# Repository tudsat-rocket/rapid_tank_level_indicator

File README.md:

# rapid_tank_level_indicator
Flex PCB to be mounted to the outside of the rocket's propellant tank to measure it's fillig level.

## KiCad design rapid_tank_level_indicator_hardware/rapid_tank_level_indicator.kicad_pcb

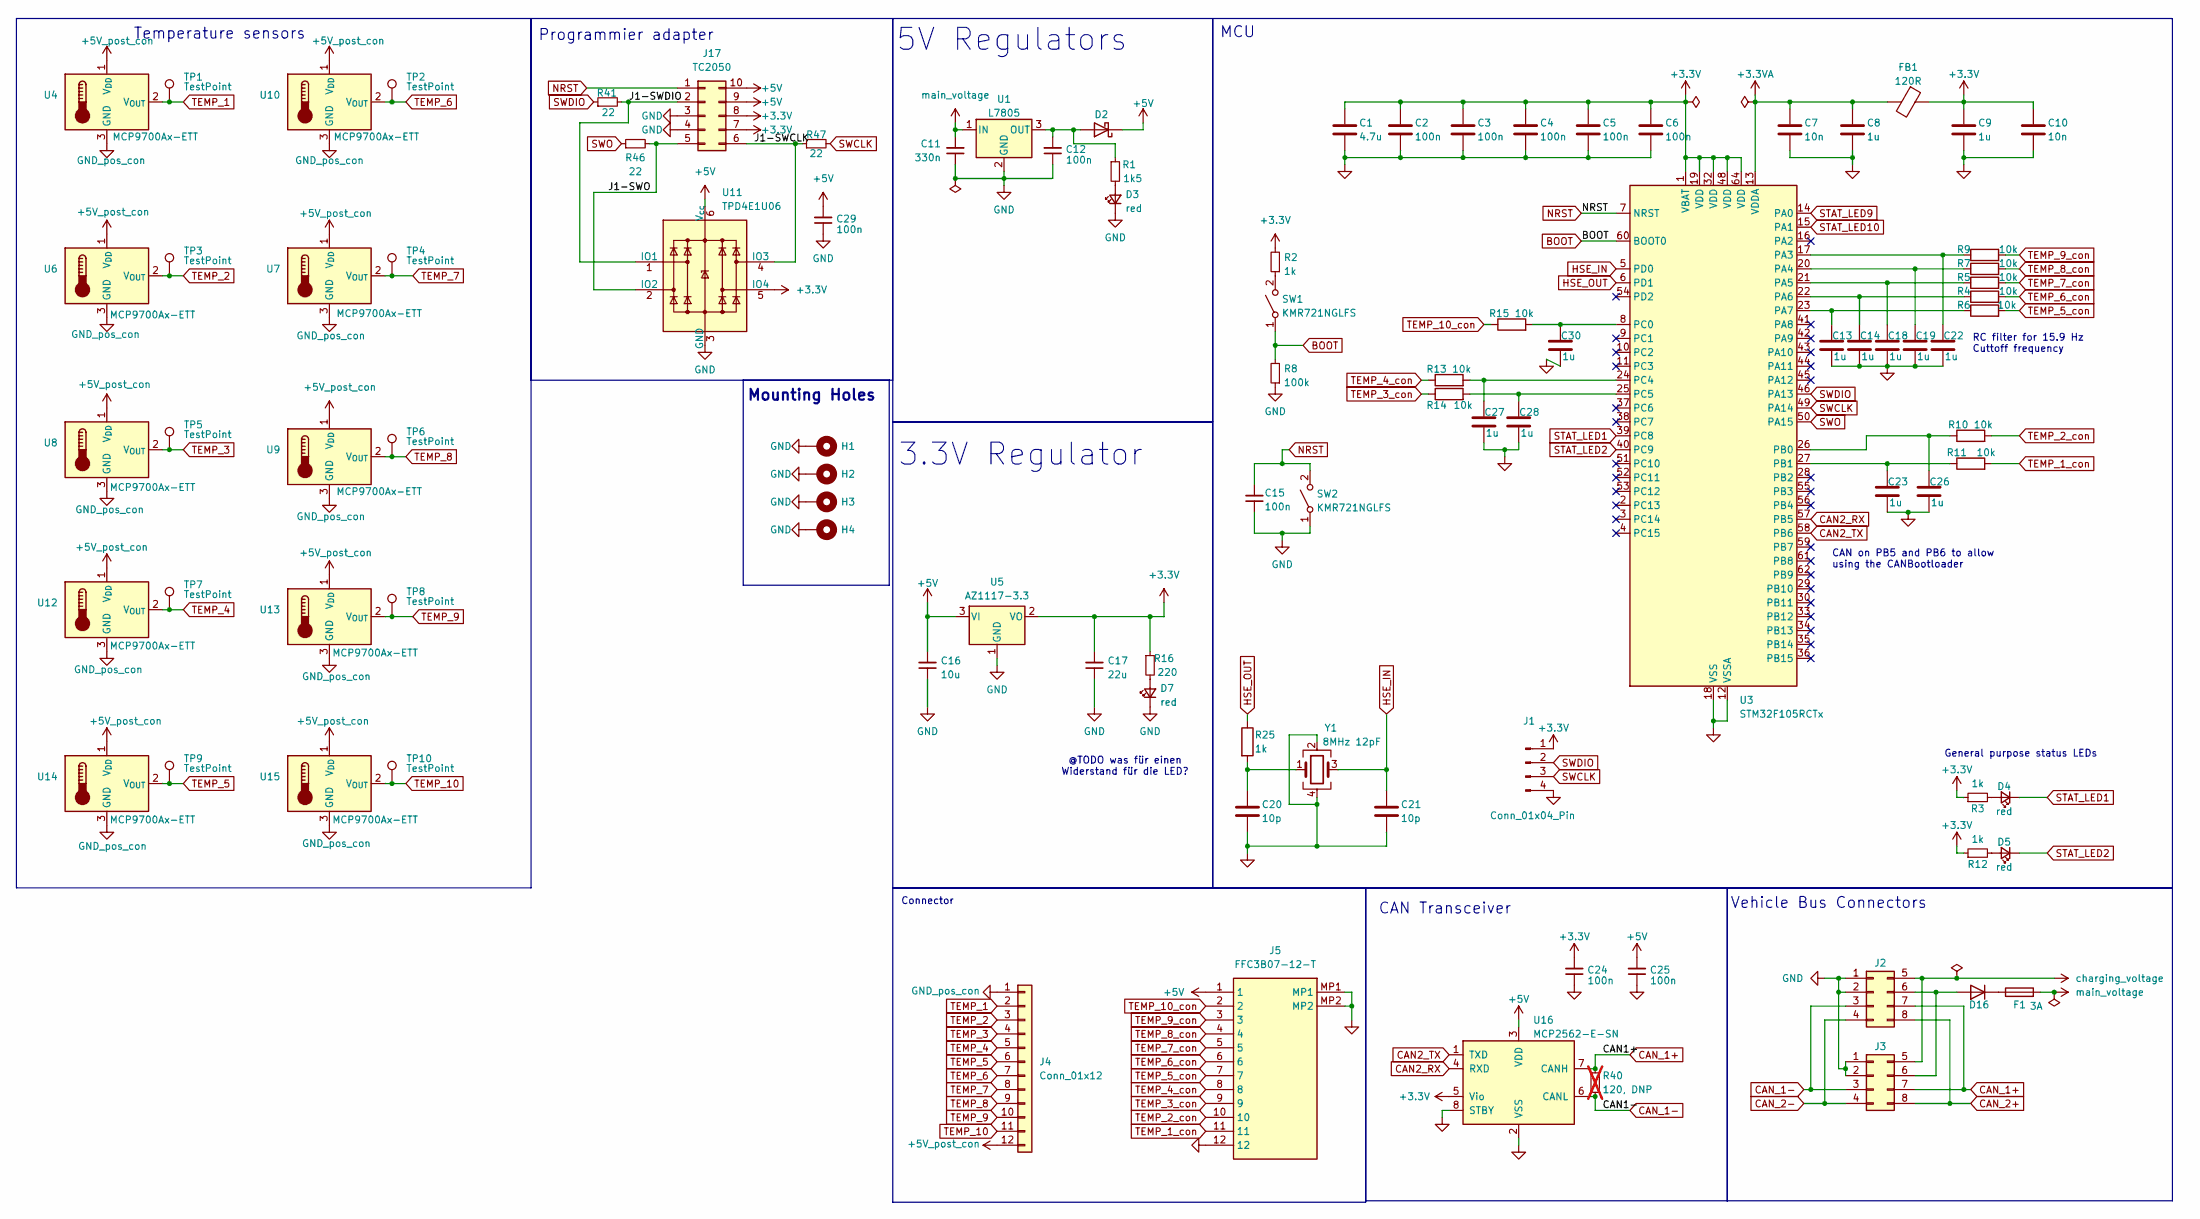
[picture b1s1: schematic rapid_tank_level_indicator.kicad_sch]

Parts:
C1: 4.7u; C_0402_1005Metric; LCSC# C368809
C2, C3, C4, C5, C6, C12, C24, C25, C29: 100n; C_0402_1005Metric; LCSC# C77020
C7, C10: 10n; C_0402_1005Metric; LCSC# C60133
C8, C9: 1u; C_0402_1005Metric; LCSC# C52923
C11: 330n; C_0603_1608Metric; Part# CL10B334KO8NNNC; LCSC# C159798
C13, C14, C18, C19, C22, C23, C26, C27, C28, C30: 1u; C_0402_1005Metric
C15: 100n; C_0402_1005Metric; Part# CL10B104KB8NNNC; LCSC C1525
C16: 10u; C_0402_1005Metric; Part# CL31B106KAHNNNE; LCSC C76991
C17: 22u; C_0402_1005Metric; Part# GRM155R60J226ME11D; LCSC C415703
C20, C21: 10p; C_0402_1005Metric; LCSC# C76946
D2: RB070MM-30TR; D_SOD-123F; LCSC # C162059
D3: red; LED_0603_1608Metric; LCSC# C2286
D4, D5: red; LED_0603_1608Metric; LCSC C2286
D7: red; LED_0603_1608Metric; Part# 19-213/RSC-BS2T2B/3T; LCSC# C474026
D16: D; D_SMA; LCSC# C5140034
F1: 3A; Fuse_0603_1608Metric_Pad1.05x0.95mm_HandSolder; LCSC# C311062
FB1: 120R; L_0603_1608Metric; Part# BLM18PG121SN1D; LCSC# C14709
H1, H2, H3, H4: MountingHole_Pad; MountingHole_3.2mm_M3_Pad_Via; Part# N/A; DigiKey# N/A
J1: Conn_01x04_Pin; PinHeader_1x04_P1.27mm_Vertical_SMD_Pin1Left
J2, J3: Conn_02x04_Top_Bottom; Molex_Micro-Fit_3.0_43045-0800_2x04_P3.00mm_Horizontal; LCSC# x
J4: Conn_01x12; FFC3B07_pad
J5: FFC3B07-12-T; FFC3B0712T; Mouser Part Number 640-FFC3B07-12-T
J17: TC2050; Tag-Connect_TC2050-IDC-FP_2x05_P1.27mm_Vertical; LCSC# x
R1: 1k5; R_0402_1005Metric; Part# ESR03EZPJ221; LCSC# C112291
R2: 1k; R_0402_1005Metric; Part# RC0603FR-0710KL; LCSC C11702
R3, R12: 1k; R_0402_1005Metric; LCSC C11702
R4, R5, R6, R7, R9, R10, R11, R13, R14, R15: 10k; R_0402_1005Metric
R8: 100k; R_0402_1005Metric; Part# RC0603FR-0710KL; LCSC C25741
R16: 220; R_0402_1005Metric; Part# ESR03EZPJ221; LCSC# C112291
R25: 1k; R_0402_1005Metric; LCSC# C21190
R40: 120, DNP; R_0603_1608Metric_Pad0.98x0.95mm_HandSolder; LCSC# x; not fitted
R41, R46, R47: 22; R_0402_1005Metric; Part# RC0603FR-0710KL; LCSC C25092
SW1, SW2: KMR721NGLFS; SW_Push_1P1T_NO_CK_KMR2; Part# KMR721NGLFS; LCSC C2911418
TP1, TP2, TP3, TP4, TP5, TP6, TP7, TP8, TP9, TP10: TestPoint; TestPoint_Pad_D1.0mm
U1: L7805; TO-252-2; Part# L7805CDT-TR; LCSC# C310413
U3: STM32F105RCTx; LQFP-64_10x10mm_P0.5mm; LCSC# C8345
U4, U6, U7, U8, U9, U10, U12, U13, U14, U15: MCP9700Ax-ETT; SOT-23; LCSC C127949
U5: AZ1117-3.3; SOT-223-3_TabPin2; LCSC C92102
U11: TPD4E1U06; SOT-563; LCSC C527516
U16: MCP2562-E-SN; SOIC-8_3.9x4.9mm_P1.27mm; Part# MCP2562T-E/SN; LCSC# C191417
Y1: 8MHz 12pF; Crystal_SMD_5032-4Pin_5.0x3.2mm; Part# 5TJ480000NYLBC; LCSC# C2149245

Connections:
+3.3V: C1.1, C2.1, C3.1, C4.1, C5.1, C6.1, C9.1, C10.1, C17.2, C24.2, FB1.1, J1.1, J17.7, J17.8, R2.2, R3.1, R12.1, R16.1, U3.1 (VBAT), U3.19 (VDD), U3.32 (VDD), U3.48 (VDD), U3.64 (VDD), U5.2 (VO), U11.5 (IO4), U16.5 (Vio)
+3.3VA: C7.1, C8.1, FB1.2, U3.13 (VDDA)
+5V: C16.2, C25.2, C29.2, D2.1 (K), J5.1, J17.9, J17.10, U5.3 (VI), U11.6 (V_{cc}), U16.3 (VDD)
+5V_post_con: J4.12, U4.1 (V_{DD}), U6.1 (V_{DD}), U7.1 (V_{DD}), U8.1 (V_{DD}), U9.1 (V_{DD}), U10.1 (V_{DD}), U12.1 (V_{DD}), U13.1 (V_{DD}), U14.1 (V_{DD}), U15.1 (V_{DD})
/J1-SWCLK: J17.6, R47.1, U11.4 (IO3)
/J1-SWDIO: J17.2, R41.2, U11.1 (IO1)
/J1-SWO: J17.5, R46.2, U11.2 (IO2)
BOOT: R8.2, SW1.1 (A), U3.60 (BOOT0)
CAN2_RX: U3.57 (PB5), U16.4 (RXD)
CAN2_TX: U3.58 (PB6), U16.1 (TXD)
CAN_1+: J2.7, J3.7, R40.1, U16.7 (CANH)
CAN_1-: J2.3, J3.3, R40.2, U16.6 (CANL)
CAN_2+: J2.8, J3.8
CAN_2-: J2.4, J3.4
GND: C1.2, C2.2, C3.2, C4.2, C5.2, C6.2, C7.2, C8.2, C9.2, C10.2, C11.1, C12.1, C13.2, C14.2, C15.1, C16.1, C17.1, C18.2, C19.2, C20.2, C21.2, C22.2, C23.2, C24.1, C25.1, C26.2, C27.2, C28.2, C29.1, C30.2, D3.1 (K), D7.1 (K), H1.1 (1_1), H2.1 (1_1), H3.1 (1_1), H4.1 (1_1), J1.4, J2.1, J2.2, J3.1, J3.2, J5.12, J5.MP1, J5.MP2, J17.3, J17.4, R8.1, SW2.1 (A), U1.2 (GND), U3.12 (VSSA), U3.18 (VSS), U3.31 (VSS), U3.47 (VSS), U3.63 (VSS), U5.1 (GND), U11.3 (GND), U16.2 (VSS), U16.8 (STBY), Y1.2, Y1.4
GND_pos_con: J4.1, U4.3 (GND), U6.3 (GND), U7.3 (GND), U8.3 (GND), U9.3 (GND), U10.3 (GND), U12.3 (GND), U13.3 (GND), U14.3 (GND), U15.3 (GND)
HSE_IN: C21.1, U3.5 (PD0), Y1.3
HSE_OUT: R25.1, U3.6 (PD1)
NRST: C15.2, J17.1, SW2.2 (B), U3.7 (NRST)
unnamed: C20.1, R25.2, Y1.1
unnamed: C12.2, D2.2 (A), R1.1, U1.3 (OUT)
unnamed: D3.2 (A), R1.2
unnamed: D4.2 (A), R3.2
unnamed: D5.2 (A), R12.2
unnamed: D7.2 (A), R16.2
unnamed: D16.2 (A), J2.6, J3.6
unnamed: D16.1 (K), F1.1
unnamed: R2.1, SW1.2 (B)
unnamed: C22.1, R9.1, U3.17 (PA3)
unnamed: C19.1, R7.1, U3.20 (PA4)
unnamed: C18.1, R5.1, U3.21 (PA5)
unnamed: C14.1, R4.1, U3.22 (PA6)
unnamed: C13.1, R6.1, U3.23 (PA7)
unnamed: C26.1, R10.1, U3.26 (PB0)
unnamed: C23.1, R11.1, U3.27 (PB1)
unnamed: C30.1, R15.2, U3.8 (PC0)
unnamed: C27.1, R13.2, U3.24 (PC4)
unnamed: C28.1, R14.2, U3.25 (PC5)
STAT_LED1: D4.1 (K), U3.39 (PC8)
STAT_LED2: D5.1 (K), U3.40 (PC9)
STAT_LED9: U3.14 (PA0)
STAT_LED10: U3.15 (PA1)
SWCLK: J1.3, R47.2, U3.49 (PA14)
SWDIO: J1.2, R41.1, U3.46 (PA13)
SWO: R46.1, U3.50 (PA15)
TEMP_1: J4.2, TP1.1 (1_1), U4.2 (V_{OUT})
TEMP_1_con: J5.11, R11.2
TEMP_2: J4.3, TP3.1 (1_1), U6.2 (V_{OUT})
TEMP_2_con: J5.10, R10.2
TEMP_3: J4.4, TP5.1 (1_1), U8.2 (V_{OUT})
TEMP_3_con: J5.9, R14.1
TEMP_4: J4.5, TP7.1 (1_1), U12.2 (V_{OUT})
TEMP_4_con: J5.8, R13.1
TEMP_5: J4.6, TP9.1 (1_1), U14.2 (V_{OUT})
TEMP_5_con: J5.7, R6.2
TEMP_6: J4.7, TP2.1 (1_1), U10.2 (V_{OUT})
TEMP_6_con: J5.6, R4.2
TEMP_7: J4.8, TP4.1 (1_1), U7.2 (V_{OUT})
TEMP_7_con: J5.5, R5.2
TEMP_8: J4.9, TP6.1 (1_1), U9.2 (V_{OUT})
TEMP_8_con: J5.4, R7.2
TEMP_9: J4.10, TP8.1 (1_1), U13.2 (V_{OUT})
TEMP_9_con: J5.3, R9.2
TEMP_10: J4.11, TP10.1 (1_1), U15.2 (V_{OUT})
TEMP_10_con: J5.2, R15.1
charging_voltage: J2.5, J3.5
main_voltage: C11.2, F1.2, U1.1 (IN)

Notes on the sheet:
Connector
Temperature sensors
CAN Transceiver
Mounting Holes
5V Regulators
MCU
@TODO was für einen Widerstand für die LED?
RC filter for 15.9 Hz Cuttoff frequency
3.3V Regulator
Programmier adapter
CAN on PB5 and PB6 to allow using the CANBootloader
General purpose status LEDs
Vehicle Bus Connectors

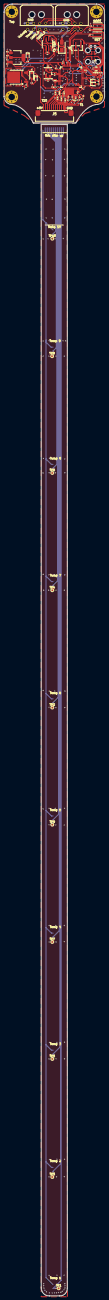
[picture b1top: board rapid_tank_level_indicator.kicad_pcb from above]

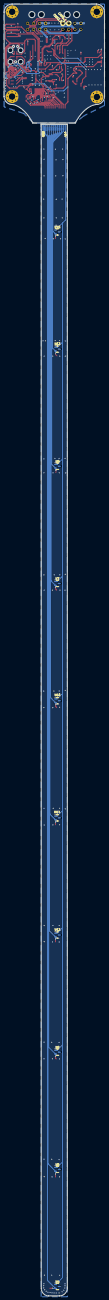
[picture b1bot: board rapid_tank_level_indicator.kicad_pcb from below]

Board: 2 copper layers, 50.0 x 643.1 mm, 97 parts (11 on the bottom side), 65 nets.

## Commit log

2026-04-27 add connector and rc-filter
